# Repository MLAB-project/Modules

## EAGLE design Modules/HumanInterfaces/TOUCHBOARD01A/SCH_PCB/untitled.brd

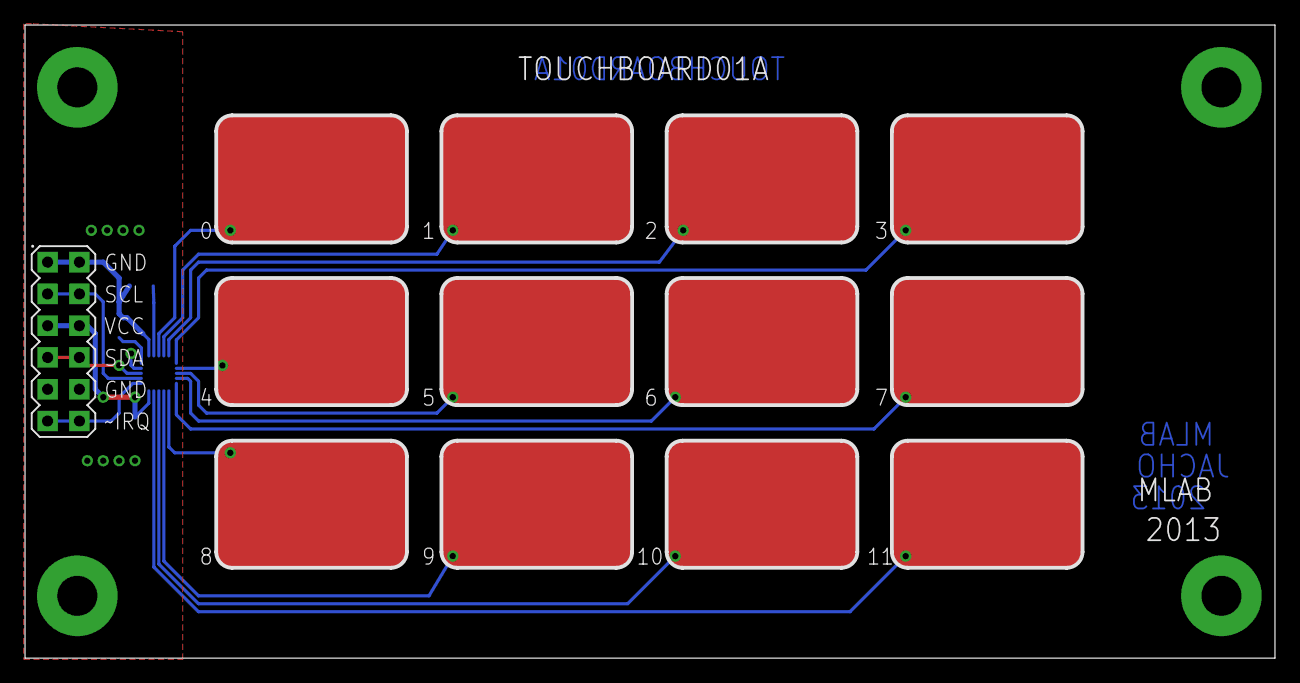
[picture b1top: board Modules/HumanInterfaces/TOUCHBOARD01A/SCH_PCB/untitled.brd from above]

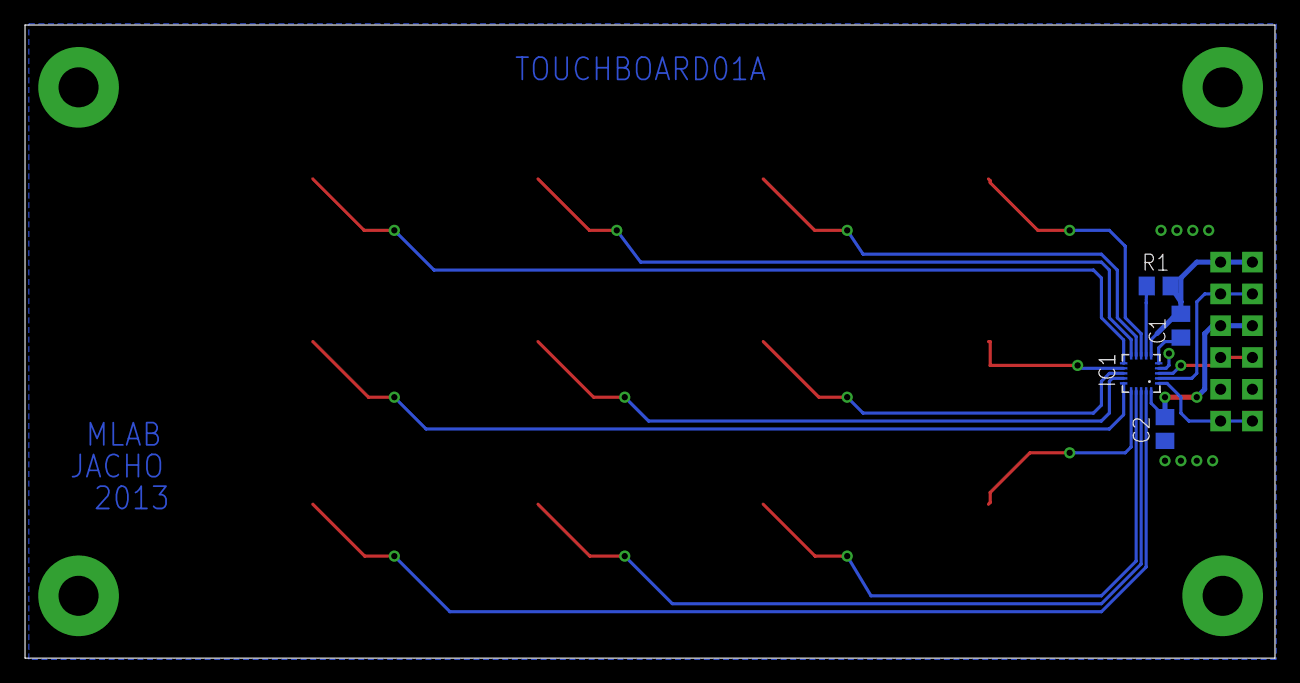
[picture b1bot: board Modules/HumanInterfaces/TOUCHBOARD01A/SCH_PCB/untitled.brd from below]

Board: 2 copper layers, 99.9 x 50.6 mm, 21 parts (4 on the bottom side), 19 nets.

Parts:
C1, C2: 100nF; C0805
IC1: MPR121; QFN-20-0.4MM
R1: 75k 1%; 0805
SV1: MA06-2
U$1, U$2, U$3, U$4, U$5, U$6, U$7, U$8, U$9, U$10, U$11, U$12: TL_DOTYK_10_15; PLOSKA10_15
X1, X2, X3, X4: SROUB3M

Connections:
GND: C1.2, C2.2, IC1.4, IC1.6, R1.1, SV1.1, SV1.2, SV1.9, SV1.10, X1.P$1, X2.P$1, X3.P$1, X4.P$1
KEY0: IC1.8, U$1.P$1
KEY1: IC1.9, U$2.P$1
KEY2: IC1.10, U$3.P$1
KEY3: IC1.11, U$4.P$1
KEY4: IC1.12, U$5.P$1
KEY5: IC1.13, U$6.P$1
KEY6: IC1.14, U$7.P$1
KEY7: IC1.15, U$8.P$1
KEY8: IC1.16, U$9.P$1
KEY9: IC1.17, U$10.P$1
KEY10: IC1.18, U$11.P$1
KEY11: IC1.19, U$12.P$1
REXT: IC1.7, R1.2
SCL: IC1.2, SV1.3, SV1.4
SDA: IC1.3, SV1.7, SV1.8
VCC: C2.1, IC1.20, SV1.5, SV1.6
VREG: C1.1, IC1.5
~IRQ: IC1.1, SV1.11, SV1.12

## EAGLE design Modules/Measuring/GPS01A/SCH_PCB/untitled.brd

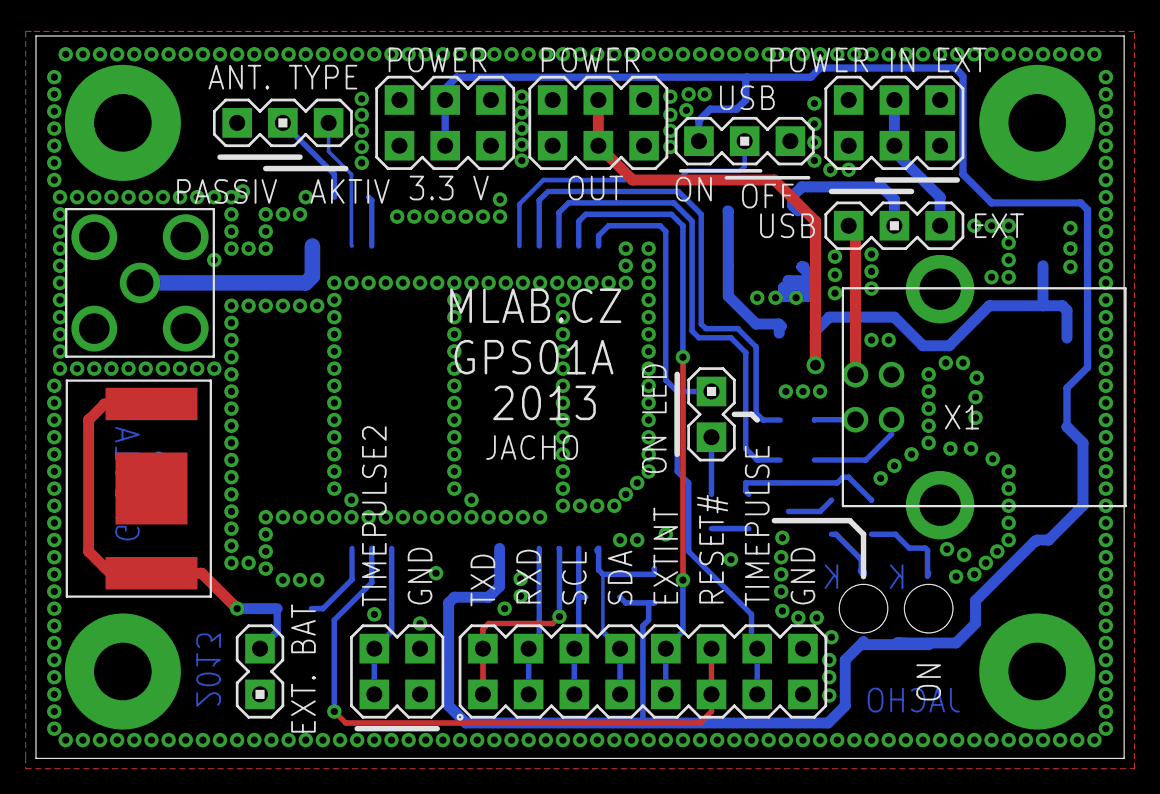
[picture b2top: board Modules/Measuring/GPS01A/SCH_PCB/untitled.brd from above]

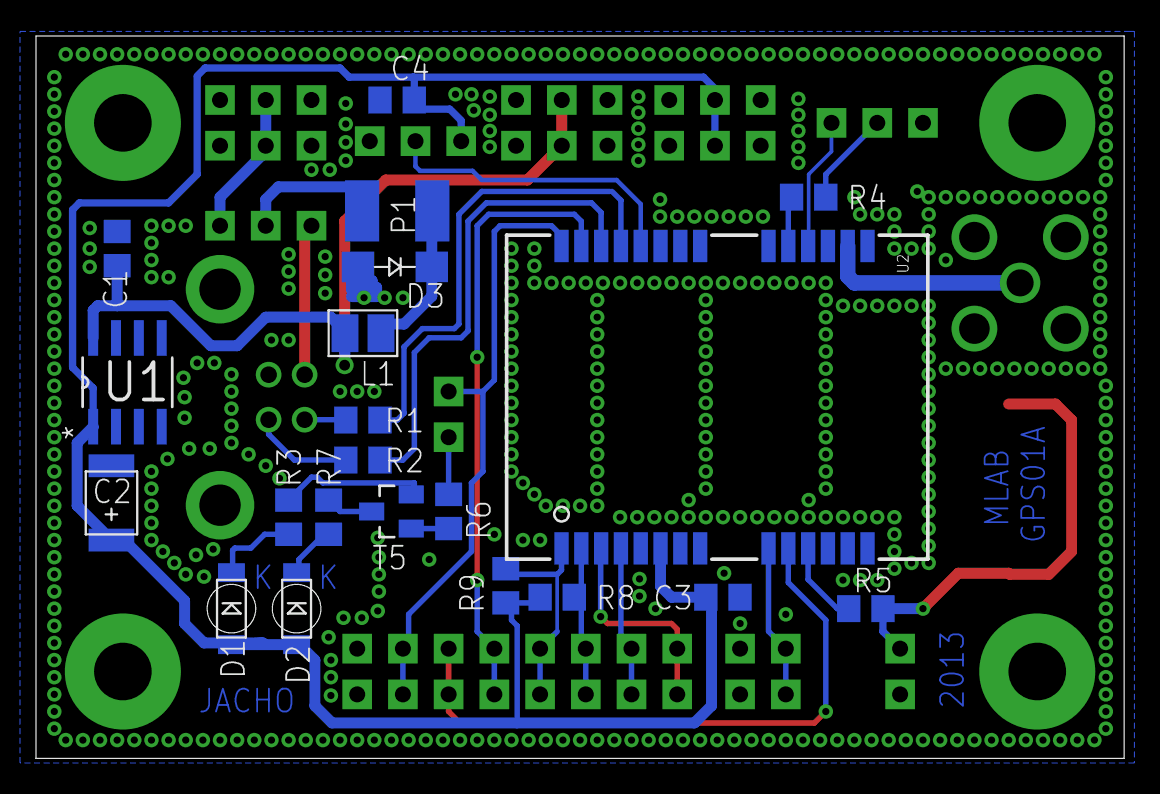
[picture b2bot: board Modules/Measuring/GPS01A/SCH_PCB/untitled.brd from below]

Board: 2 copper layers, 60.5 x 40.1 mm, 38 parts (21 on the bottom side), 31 nets.

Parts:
C1, C3, C4: 100nF; C0805
C2: 10uF; B
D1: CERVENA; 1206
D2: ZELENA; 1206
D3: M4; SMA
L1: NL322522T-101K; 1210
P1: 1812
R1, R2: 33; 0805
R3, R7: 150R; 0805
R4: 10; 0805
R5, R6: 100; 0805
R8, R9: 4k7; 0805
SV1, SV4, SV8: MA03-1
SV2, SV9, SV10: MA03-2
SV3, SV7: MA02-1
SV5: MA02-2
SV6: MA08-2
SW1: 1.55V; BAT6MM8
SW2: SMA
T1: BC817; SOT23
U1: LE33CD-TR; SOIC127P600X175-8N
U2: UBLOX-LEA-6
X1: USB_B
X2, X3, X4, X5: SROUB3M

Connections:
+3.3V: C2.+, C3.1, C4.1, D1.A, D2.A, R8.2, R9.2, SV8.1, SV9.3, SV9.4, U1.1, U2.6
EXTINT: SV6.9, SV6.10, U2.27
GND: C1.2, C2.-, C3.2, C4.2, D3.A, R3.1, SV2.1, SV2.2, SV2.5, SV2.6, SV3.2, SV4.1, SV5.3, SV5.4, SV6.15, SV6.16, SV8.3, SV9.1, SV9.2, SV9.5, SV9.6, SV10.1, SV10.2, SV10.5, SV10.6, SW1.-, SW2.-1, SW2.-2, SW2.-3, SW2.-4, T1.2, U1.2, U1.3, U1.5, U1.6, U1.7, U2.7, U2.13, U2.14, U2.15, U2.17, X1.4, X1.GND, X1.GND2, X2.P$1, X3.P$1, X4.P$1, X5.P$1
unnamed: SW2.+, U2.16
unnamed: SV1.1, SV2.3, SV2.4
unnamed: R1.1, X1.2
unnamed: R2.1, X1.3
unnamed: C1.1, L1.P$2, SV10.3, SV10.4, U1.8
unnamed: P1.2, SV1.2
unnamed: D1.K, R3.2
unnamed: R4.2, U2.19
unnamed: D3.K, L1.P$1, P1.1
unnamed: R4.1, SV4.2
unnamed: R5.1, U2.11
unnamed: R5.2, SV3.1, SW1.1+, SW1.2+
unnamed: SV5.1, SV5.2, U2.9
unnamed: D2.K, R7.2
unnamed: R7.1, T1.3
unnamed: R6.2, T1.1
unnamed: R6.1, SV7.1
RESET_N: SV6.11, SV6.12, U2.10
RXD: SV6.3, SV6.4, U2.4
SCL: R8.1, SV6.5, SV6.6, U2.2
SDA: R9.1, SV6.7, SV6.8, U2.1
TIMEPULSE: SV6.13, SV6.14, SV7.2, U2.28
TXD: SV6.1, SV6.2, U2.3
USB_DET: SV8.2, U2.24
USB_DM: R1.2, U2.25
USB_DP: R2.2, U2.26
VCC_RF: SV4.3, U2.18
VDD_USB: SV1.3, X1.1

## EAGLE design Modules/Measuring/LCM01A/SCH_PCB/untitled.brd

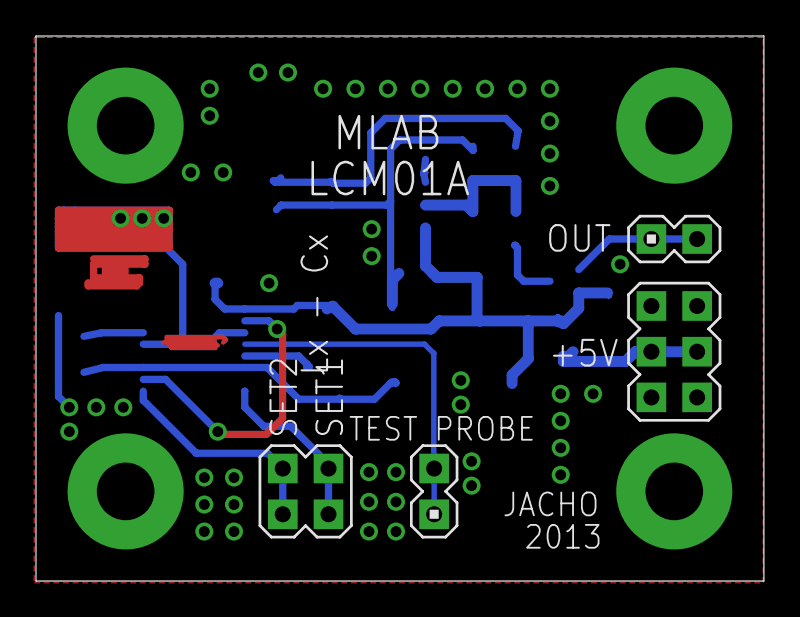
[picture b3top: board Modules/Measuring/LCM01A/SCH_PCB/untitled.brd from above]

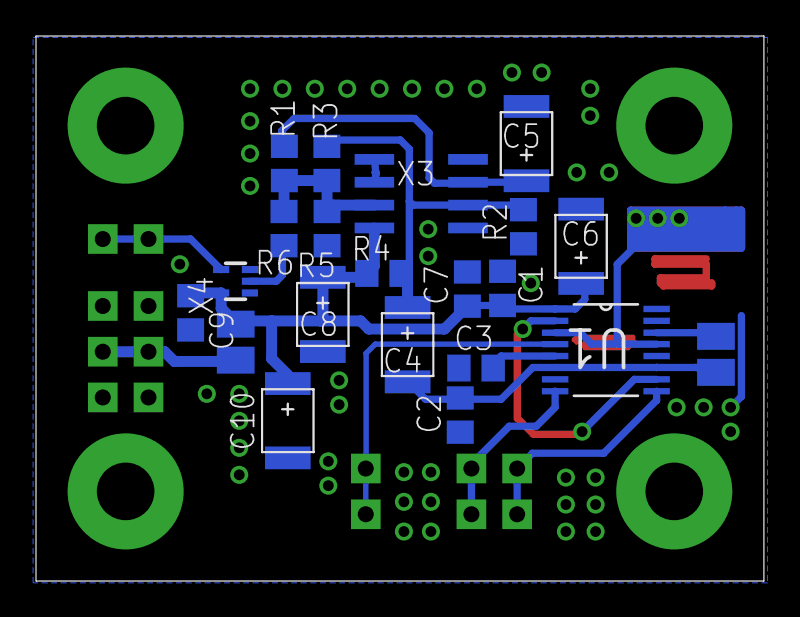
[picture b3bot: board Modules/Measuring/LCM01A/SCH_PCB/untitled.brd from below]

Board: 2 copper layers, 40.4 x 30.3 mm, 30 parts (21 on the bottom side), 17 nets.

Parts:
C1, C9: 100nF; C0805
C2: 680pF; C0805
C3: 1nF presny; C0805
C4: 10u/10V; B
C5, C6: 4u7/10V; B
C7: C0805
C8, C10: B
CX-LX: SPEC_805
L1: 68uH presny; 1210
L2: 1210
R1: 47k; 0805
R2, R3, R4: 100k; 0805
R5: 1k; 0805
R6: 0; 0805
SV1: MA02-2
SV2: MA03-2
SV3, SV4: MA02-1
U1: ADG888YRUZ; SOP65P640X120-16N
X1, X2, X6, X7: SROUB3M
X3: LM311; SO8
X4: 74HC1G14; SOT353

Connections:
C+: CX-LX.2, U1.3, U1.13
GND: C1.2, C2.1, C3.1, C5.-, C6.-, C7.2, C8.-, C9.2, C10.-, CX-LX.1, R2.1, SV2.1, SV2.2, SV2.5, SV2.6, U1.15, U1.16, X1.P$1, X2.P$1, X3.1, X3.4, X4.3, X6.P$1, X7.P$1
unnamed: C2.2, C4.-, L1.P$1, U1.6, U1.11
unnamed: X3.5, X3.6
unnamed: C3.2, U1.5
unnamed: U1.2, U1.10
unnamed: SV1.1, SV1.2, U1.8
unnamed: SV3.1, SV3.2, U1.4
unnamed: L1.P$2, U1.14
unnamed: C5.+, R1.2, X3.3
unnamed: R1.1, R3.1, R5.1, R6.2, X3.7
unnamed: SV1.3, SV1.4, U1.9
unnamed: R6.1, X4.2
unnamed: C4.+, R2.2, R3.2, R4.1, X3.2
unnamed: SV4.1, SV4.2, X4.4
NAP: C1.1, C6.+, C7.1, C8.+, C9.1, C10.+, L2.P$1, R4.2, U1.1, X3.8, X4.5
VCC: L2.P$2, SV2.3, SV2.4

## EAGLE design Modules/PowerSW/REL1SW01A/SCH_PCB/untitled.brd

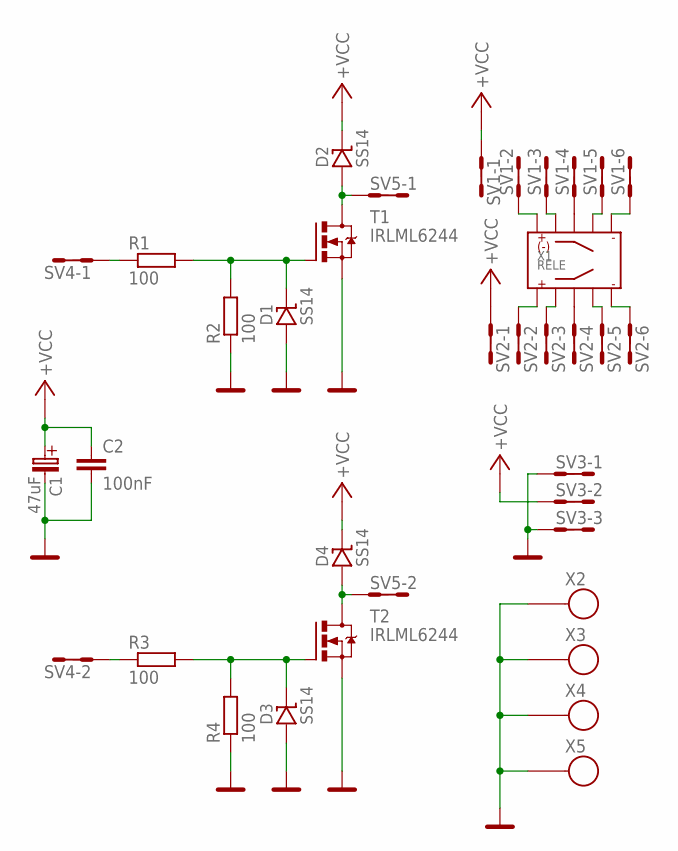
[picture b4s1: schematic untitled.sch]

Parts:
C1: 47uF; B
C2: 100nF; C0805
D1, D2, D3, D4: SS14; SMA
R1, R2, R3, R4: 100; 0805
SV1, SV2: MA06-2
SV3: MA03-2
SV4, SV5: MA02-2
T1, T2: IRLML6244; SOT23
X1: RELE
X2, X3, X4, X5: SROUB3M

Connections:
+VCC: C1.+ (C_EL+), C2.1, D2.K, D4.K, SV1.1, SV1.2, SV2.1, SV2.2, SV3.3, SV3.4
GND: C1.- (C_EL-), C2.2, D1.A, D3.A, R2.1, R4.1, SV3.1, SV3.2, SV3.5, SV3.6, T1.2 (S), T2.2 (S), X2.P$1, X3.P$1, X4.P$1, X5.P$1
unnamed: D2.A, SV5.1, SV5.2, T1.3 (D)
unnamed: D1.K, R1.2, R2.2, T1.1 (G)
unnamed: D4.A, SV5.3, SV5.4, T2.3 (D)
unnamed: D3.K, R3.2, R4.2, T2.1 (G)
unnamed: SV1.3, SV1.4, X1.10
unnamed: SV1.5, SV1.6, X1.9
unnamed: SV1.7, SV1.8, X1.8
unnamed: SV1.9, SV1.10, X1.7
unnamed: SV1.11, SV1.12, X1.6
unnamed: SV2.3, SV2.4, X1.1
unnamed: SV2.5, SV2.6, X1.2
unnamed: SV2.7, SV2.8, X1.3
unnamed: SV2.9, SV2.10, X1.4
unnamed: SV2.11, SV2.12, X1.5
unnamed: R1.1, SV4.1, SV4.2
unnamed: R3.1, SV4.3, SV4.4

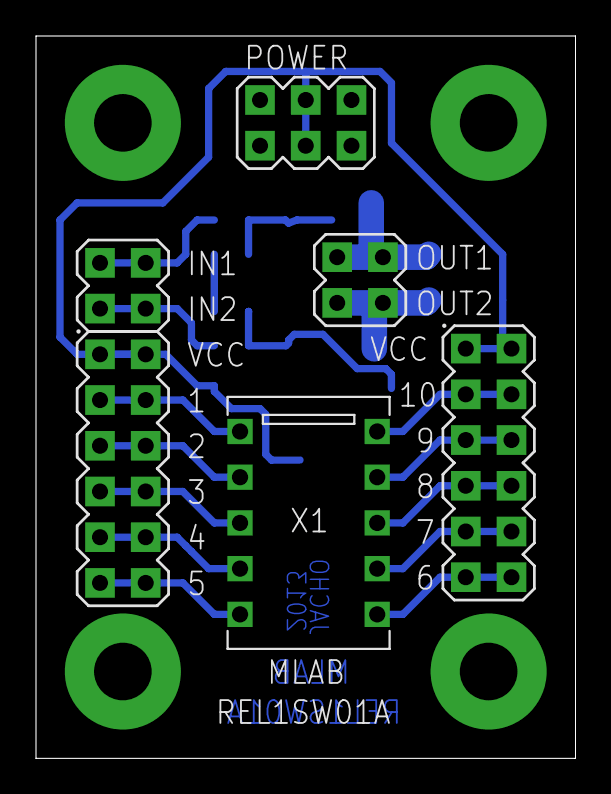
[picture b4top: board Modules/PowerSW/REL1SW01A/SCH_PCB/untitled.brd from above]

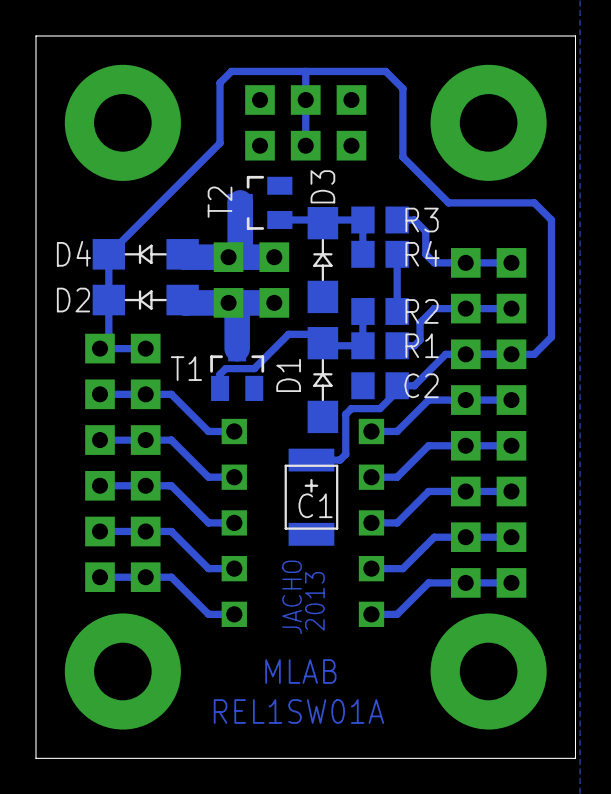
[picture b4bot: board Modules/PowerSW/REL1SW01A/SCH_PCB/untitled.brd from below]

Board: 2 copper layers, 30.0 x 40.1 mm, 22 parts (12 on the bottom side), 18 nets.

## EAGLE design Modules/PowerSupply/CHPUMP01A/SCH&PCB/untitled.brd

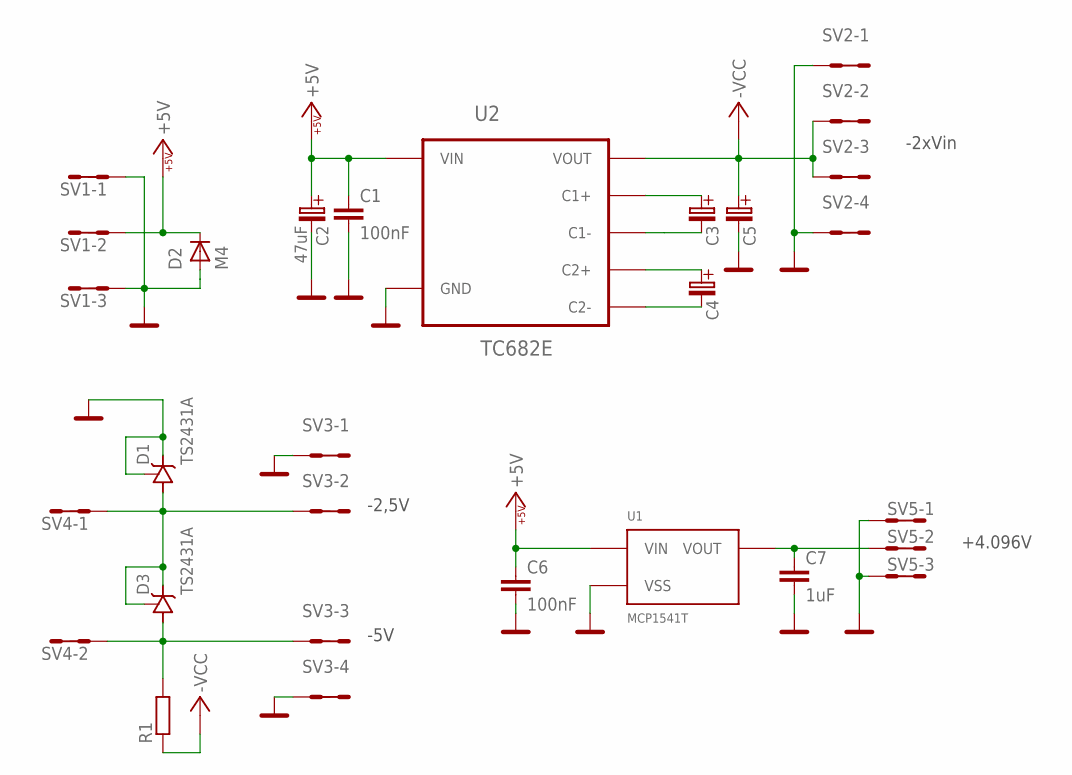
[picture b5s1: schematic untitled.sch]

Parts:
C1, C6: 100nF; C0805
C2: 47uF; C
C3, C4, C5: C
C7: 1uF; C0805
D1, D3: TS2431A; SOT23
D2: M4; SMA
R1: R0805; 0805
SV1, SV5: MA03-2
SV2, SV3: MA04-2
SV4: MA02-2
U1: MCP1541T; SOT23
U2: TC682E; SO8

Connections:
+5V: C1.1, C2.+ (C_EL+), C6.1, D2.K (C), SV1.3, SV1.4, U1.1 (VIN), U2.6 (VIN)
-VCC: C5.+ (C_EL+), R1.1, SV2.3, SV2.4, SV2.5, SV2.6, U2.4 (VOUT)
GND: C1.2, C2.- (C_EL-), C5.- (C_EL-), C6.2, C7.2, D1.1 (K), D1.2, D2.A, SV1.1, SV1.2, SV1.5, SV1.6, SV2.1, SV2.2, SV2.7, SV2.8, SV3.1, SV3.2, SV3.7, SV3.8, SV5.1, SV5.2, SV5.5, SV5.6, U1.3 (VSS), U2.5 (GND)
unnamed: C3.- (C_EL-), U2.1 (C1-)
unnamed: C3.+ (C_EL+), U2.7 (C1+)
unnamed: C4.+ (C_EL+), U2.2 (C2+)
unnamed: C4.- (C_EL-), U2.3 (C2-)
unnamed: D3.3 (A), R1.2, SV3.5, SV3.6, SV4.3, SV4.4
unnamed: D1.3 (A), D3.1 (K), D3.2, SV3.3, SV3.4, SV4.1, SV4.2
unnamed: C7.1, SV5.3, SV5.4, U1.2 (VOUT)

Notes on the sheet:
-2,5V
-5V
+4.096V
-2xVin

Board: 2 copper layers, 22 parts (13 on the bottom side), 10 nets, no tracks yet.

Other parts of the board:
X1, X2, X3, X4: SROUB3M

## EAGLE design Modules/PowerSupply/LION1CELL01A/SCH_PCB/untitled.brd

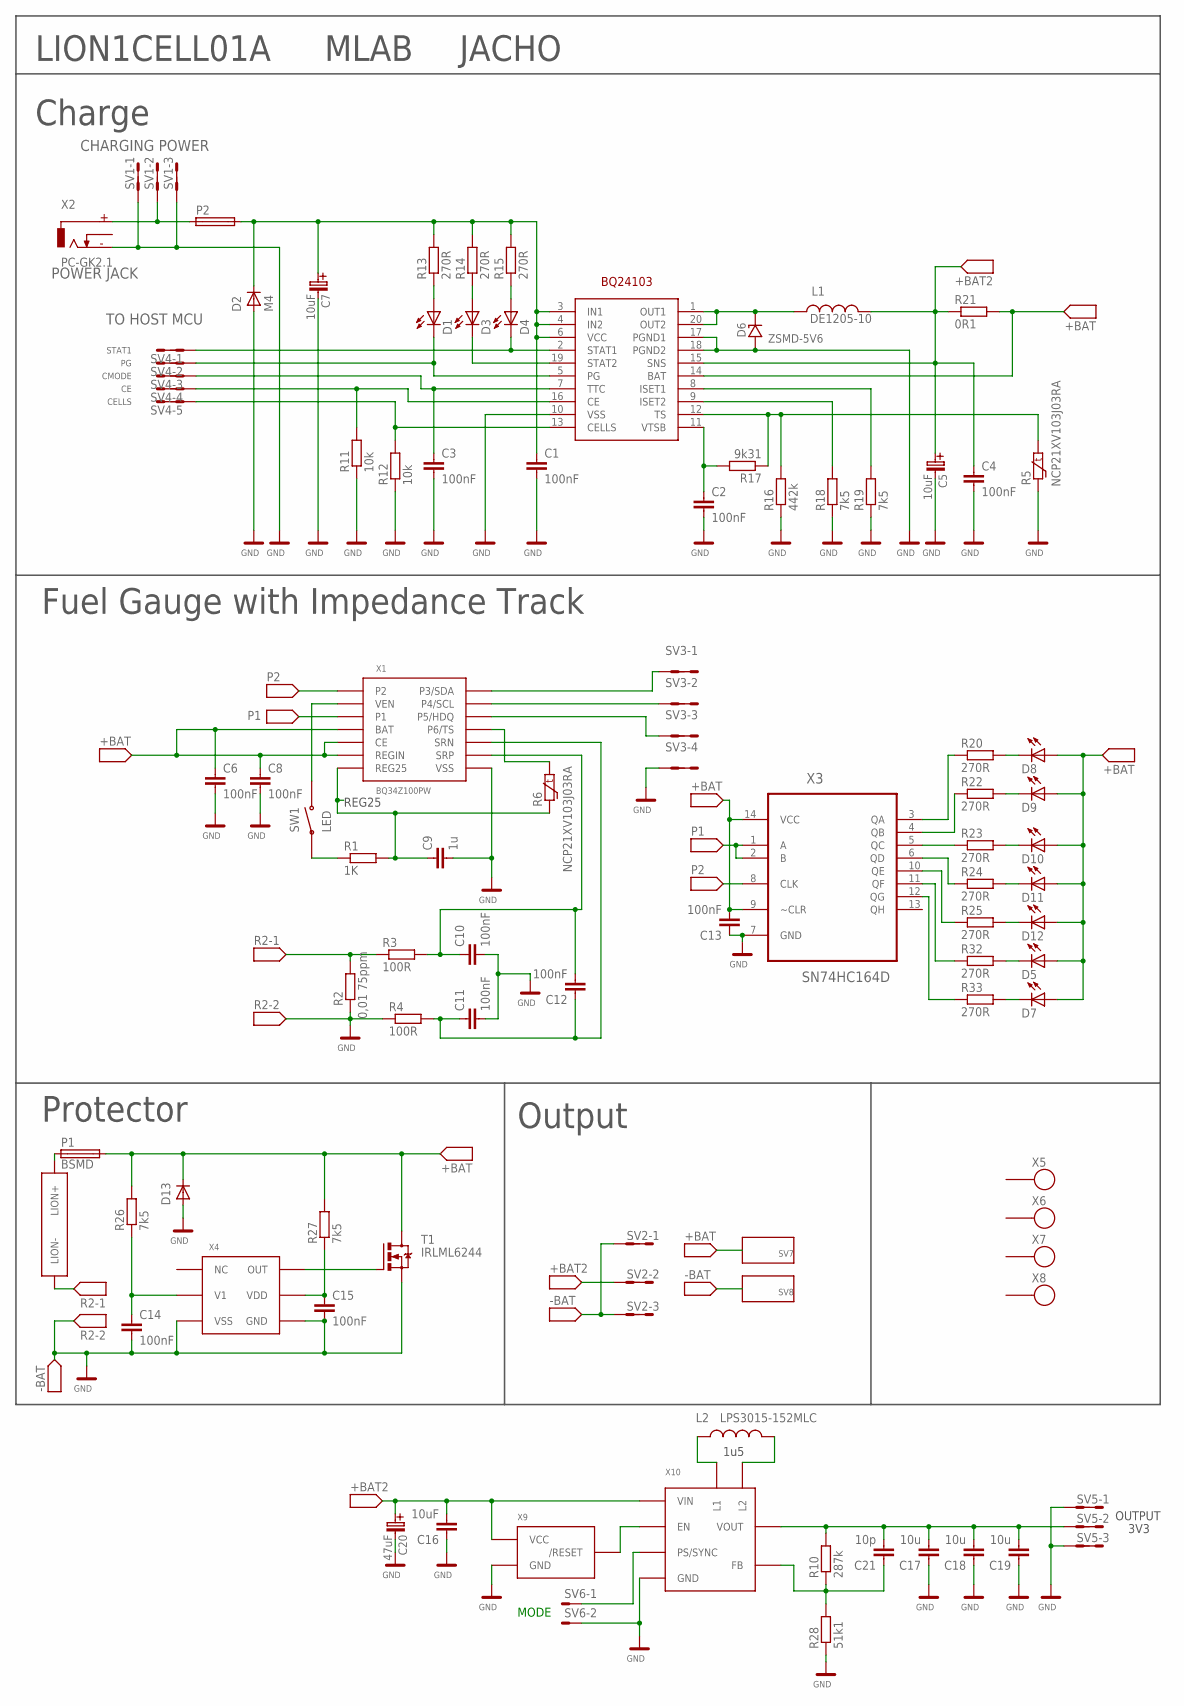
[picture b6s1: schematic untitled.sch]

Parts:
C1, C2, C3, C4, C6, C8, C10, C11, C12, C13, C14, C15: 100nF; C0805
C5, C7: 10uF; B
C9: 1u; C0805
C16: 10uF; C0805
C17, C18, C19: 10u; C0805
C20: 47uF; B
C21: 10p; 0603
D1, D3, D4, D5, D7, D8, D9, D10, D11, D12: LED1206_2; 1206_2
D2: M4; SMB
D6: ZSMD-5V6; MINIMELF
D13: D-OB.SMA; SMA
L1: DE1205-10
L2: LPS3015-152MLC; LPS3015
P1: BSMD; 2410
P2: POJISTKA_1812; 1812
R1: 1K; 0805
R2: 0,01 75ppm; 0805
R3, R4: 100R; 0805
R5, R6: NCP21XV103J03RA; 0805
R10: 287k; 0603
R11, R12: 10k; 0805
R13, R14, R15, R20, R22, R23, R24, R25, R32, R33: 270R; 0805
R16: 442k; 0805
R17: 9k31; 0805
R18, R19, R26, R27: 7k5; 0805
R21: 0R1; R2512
R28: 51k1; 0603
SV1, SV2, SV5: MA03-2
SV3: MA04-2
SV4: MA05-2
SV6: MA02-1
SV7, SV8: WAGO256
SW1: TACT-64K
T1: IRLML6244; SOT23
U1: BQ24103; RHL_R-VQFN-N20
U$2: LION1
X1: BQ34Z100PW; TSSOP14
X2: DC2.1MM
X3: SN74HC164D; SOIC127P600X175-14N
X4: BQ294602; SON_N6
X5, X6, X7, X8: SROUB3M
X9: APX809-26SA; SOT23
X10: TPS63036; DSBGA8

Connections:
+BAT: C6.1, C8.1, C13.2, D5.A, D7.A, D8.A, D9.A, D10.A, D11.A, D12.A, D13.K (C), P1.2, R21.2, R26.2, R27.2, SV7.1, SV7.A1, T1.3 (D), U1.14 (BAT), X1.4 (BAT), X1.5 (CE), X1.6 (REGIN), X3.9 (~CLR), X3.14 (VCC)
+BAT2: C4.1, C5.+ (C_EL+), C16.2, C20.+ (C_EL+), L1.P$2 (2), R21.1, SV2.3, SV2.4, U1.15 (SNS), X9.3 (VCC), X10.A1 (VIN)
EN: X9.2 (/RESET), X10.A2 (EN)
GND: C1.2, C2.2, C3.2, C4.2, C5.- (C_EL-), C6.2, C7.- (C_EL-), C8.2, C9.2, C10.2, C11.2, C13.1, C14.2, C15.2, C16.1, C17.1, C18.1, C19.1, C20.- (C_EL-), D2.A, D6.A, D13.A, R2.1, R4.1, R5.1, R11.1, R12.1, R16.1, R18.1, R19.1, R28.1, SV1.1, SV1.2, SV1.5, SV1.6, SV2.1, SV2.2, SV2.5, SV2.6, SV3.7, SV3.8, SV5.1, SV5.2, SV5.5, SV5.6, SV6.2, SV8.1, SV8.A1, T1.2 (S), U1.10 (VSS), U1.17 (PGND1), U1.18 (PGND2), X1.8 (VSS), X2.GND (-), X3.7 (GND), X4.3 (VSS), X4.4 (VSS), X4.7 (GND), X9.1 (GND), X10.C2 (GND)
unnamed: C1.1, C7.+ (C_EL+), D2.K (C), P2.2, R13.2, R14.2, R15.2, U1.3 (IN1), U1.4 (IN2), U1.6 (VCC)
unnamed: P1.1, U$2.+ (LION+), U$2.+1 (LION+)
unnamed: D6.C (K), L1.P$1 (1), U1.1 (OUT1), U1.20 (OUT2)
unnamed: D4.K (C), SV4.1, SV4.2, U1.2 (STAT1)
unnamed: D3.K (C), U1.19 (STAT2)
unnamed: D1.K (C), SV4.3, SV4.4, U1.5 (PG)
unnamed: D1.A, R13.1
unnamed: D3.A, R14.1
unnamed: D4.A, R15.1
unnamed: R12.2, SV4.9, SV4.10, U1.13 (CELLS)
unnamed: R11.2, SV4.7, SV4.8, U1.16 (CE)
unnamed: C2.1, R17.2, U1.11 (VTSB)
unnamed: R18.2, U1.9 (ISET2)
unnamed: C3.1, SV4.5, SV4.6, U1.7 (TTC)
unnamed: R19.2, U1.8 (ISET1)
unnamed: SV3.3, SV3.4, X1.13 (P4/SCL)
unnamed: SW1.P$3, SW1.P$4, X1.2 (VEN)
unnamed: R5.2, R16.2, R17.1, U1.12 (TS)
unnamed: L2.1-1 (1), L2.1-2 (1), L2.1-3 (1), X10.B1 (L1)
unnamed: R1.1, SW1.P$1, SW1.P$2
unnamed: SV6.1, X10.B2 (PS/SYNC)
unnamed: R6.2, X1.11 (P6/TS)
unnamed: C10.1, C12.2, R3.2, X1.9 (SRP)
unnamed: SV3.5, SV3.6, X1.12 (P5/HDQ)
unnamed: SV3.1, SV3.2, X1.14 (P3/SDA)
unnamed: L2.2-1 (2), L2.2-2 (2), L2.2-3 (2), X10.C1 (L2)
unnamed: C11.1, C12.1, R4.2, X1.10 (SRN)
unnamed: C17.2, C18.2, C19.2, C21.2, R10.2, SV5.3, SV5.4, X10.D1 (VOUT)
unnamed: C21.1, R10.1, R28.2, X10.D2 (FB)
unnamed: R20.1, X3.3 (QA)
unnamed: D8.K (C), R20.2
unnamed: R22.1, X3.4 (QB)
unnamed: R23.1, X3.5 (QC)
unnamed: R24.1, X3.6 (QD)
unnamed: R25.1, X3.10 (QE)
unnamed: D9.K (C), R22.2
unnamed: D11.K (C), R24.2
unnamed: D12.K (C), R25.2
unnamed: D10.K (C), R23.2
unnamed: C14.1, R26.1, X4.2 (V1)
unnamed: C15.1, R27.1, X4.5 (VDD)
unnamed: T1.1 (G), X4.6 (OUT)
unnamed: R32.1, X3.11 (QF)
unnamed: R33.1, X3.12 (QG)
unnamed: D5.K (C), R32.2
unnamed: D7.K (C), R33.2
unnamed: P2.1, SV1.3, SV1.4, X2.+
P1: X1.3 (P1), X3.1 (A), X3.2 (B)
P2: X1.1 (P2), X3.8 (CLK)
R2: R2.2, R3.1, U$2.- (LION-), U$2.-1 (LION-)
REG25: C9.1, R1.2, R6.1, X1.7 (REG25)

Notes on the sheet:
STAT1
CMODE
CELLS
POWER JACK
TO HOST MCU
CHARGING POWER
LED
Protector
Fuel Gauge with Impedance Track
Charge
Output
LION1CELL01A
MLAB
JACHO
REG25
1u5
3V3
OUTPUT
MODE

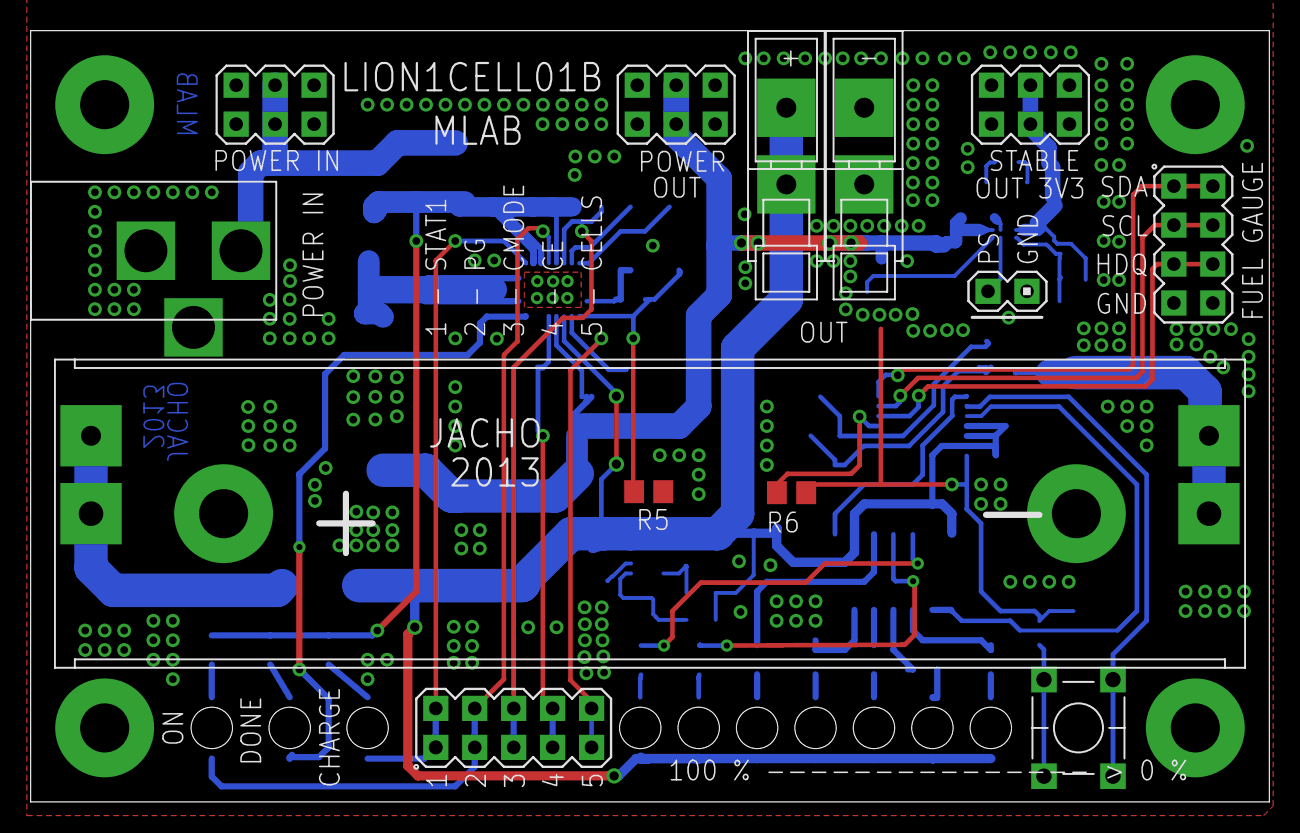
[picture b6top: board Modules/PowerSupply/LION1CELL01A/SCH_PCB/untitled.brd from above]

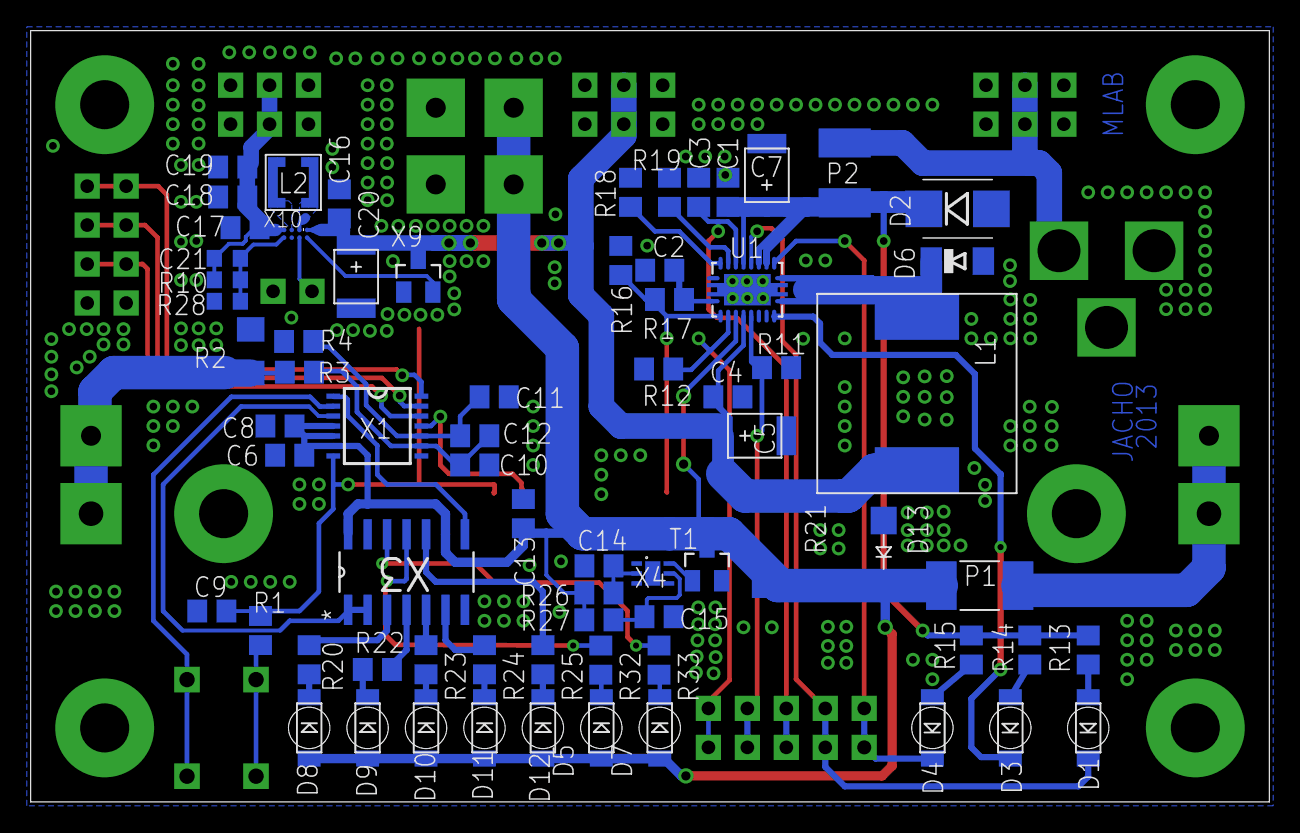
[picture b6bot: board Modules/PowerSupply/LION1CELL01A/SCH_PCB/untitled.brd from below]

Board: 2 copper layers, 80.8 x 50.3 mm, 87 parts (70 on the bottom side), 55 nets.

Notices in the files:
parts and their libraries:
SparkFun: Licensing: CC v3.0 Share-Alike You are welcome to use this library for commercial purposes.
PaJa_22: Copyright (C) PaJa 2001-2010
